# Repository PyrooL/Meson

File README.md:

# Meson
A split 3x14 keyboard with spacebars on a fourth row. Reversible MX//Alps/Choc support.

KiCAD libraries here:

- https://github.com/ai03-2725/MX_Alps_Hybrid.pretty

- https://github.com/ai03-2725/Type-C.pretty

- https://github.com/ai03-2725/random-keyboard-parts.pretty

- https://github.com/keebio/Keebio-Parts.pretty

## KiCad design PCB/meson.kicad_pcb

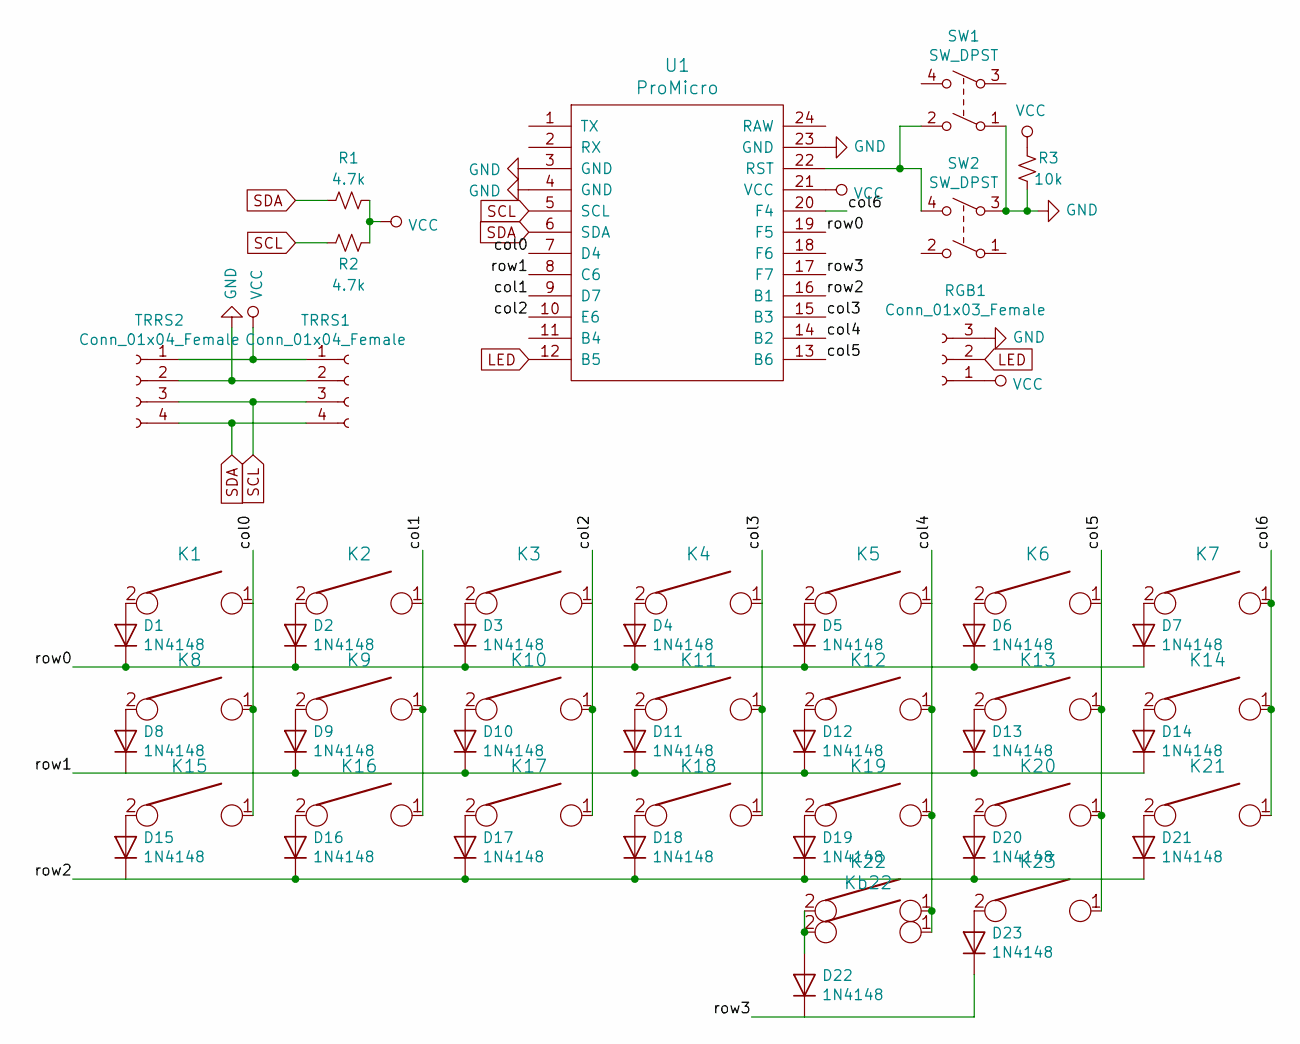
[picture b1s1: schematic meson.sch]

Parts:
D1, D2, D3, D4, D5, D6, D7, D8, D9, D10, D11, D12, D13, D14, D15, D16, D17, D18, D19, D20, D21, D22, D23: 1N4148; D_DO-35_SOD27_P7.62mm_Horizontal
K1, K2, K3, K4, K5, K6, K7, K8, K9, K10, K11, K12, K13, K14, K15, K16, K17, K18, K19, K20, K21, K22, K23: KEYSW; MX-Alps-Choc-1U-NoLED-Reversible
Kb22: KEYSW; MX-1U-NoLED-Reversible
R1, R2: 4.7k; Resistor-Hybrid
R3: 10k; Resistor-Hybrid
RGB1: Conn_01x03_Female; PinHeader_1x03_P2.54mm_Vertical
SW1, SW2: SW_DPST; SKQG-1155865
TRRS1, TRRS2: Conn_01x04_Female; TRRS-PJ-320A
U1: ProMicro; ArduinoProMicro

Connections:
/col0: K1.1, K8.1, K15.1, U1.7 (D4)
/col1: K2.1, K9.1, K16.1, U1.9 (D7)
/col2: K3.1, K10.1, K17.1, U1.10 (E6)
/col3: K4.1, K11.1, K18.1, U1.15 (B3)
/col4: K5.1, K12.1, K19.1, K22.1, Kb22.1, U1.14 (B2)
/col5: K6.1, K13.1, K20.1, K23.1, U1.13 (B6)
/col6: K7.1, K14.1, K21.1, U1.20 (F4)
/row0: D1.1 (K), D2.1 (K), D3.1 (K), D4.1 (K), D5.1 (K), D6.1 (K), D7.1 (K), U1.19 (F5)
/row1: D8.1 (K), D9.1 (K), D10.1 (K), D11.1 (K), D12.1 (K), D13.1 (K), D14.1 (K), U1.8 (C6)
/row2: D15.1 (K), D16.1 (K), D17.1 (K), D18.1 (K), D19.1 (K), D20.1 (K), D21.1 (K), U1.16 (B1)
/row3: D22.1 (K), D23.1 (K), U1.17 (F7)
GND: R3.2, RGB1.3, SW1.1, SW2.3, TRRS1.2, TRRS2.2, U1.3 (GND), U1.4 (GND), U1.23 (GND)
LED: RGB1.2, U1.12 (B5)
unnamed: D1.2 (A), K1.2
unnamed: D2.2 (A), K2.2
unnamed: D3.2 (A), K3.2
unnamed: D4.2 (A), K4.2
unnamed: D5.2 (A), K5.2
unnamed: D6.2 (A), K6.2
unnamed: D7.2 (A), K7.2
unnamed: D8.2 (A), K8.2
unnamed: D9.2 (A), K9.2
unnamed: D10.2 (A), K10.2
unnamed: D11.2 (A), K11.2
unnamed: D12.2 (A), K12.2
unnamed: D13.2 (A), K13.2
unnamed: D14.2 (A), K14.2
unnamed: D15.2 (A), K15.2
unnamed: D16.2 (A), K16.2
unnamed: D17.2 (A), K17.2
unnamed: D18.2 (A), K18.2
unnamed: D19.2 (A), K19.2
unnamed: D20.2 (A), K20.2
unnamed: D21.2 (A), K21.2
unnamed: D22.2 (A), K22.2, Kb22.2
unnamed: D23.2 (A), K23.2
unnamed: SW1.2, SW2.4, U1.22 (RST)
SCL: R2.2, TRRS1.3, TRRS2.3, U1.5 (SCL)
SDA: R1.2, TRRS1.4, TRRS2.4, U1.6 (SDA)
VCC: R1.1, R2.1, R3.1, RGB1.1, TRRS1.1, TRRS2.1, U1.21 (VCC)

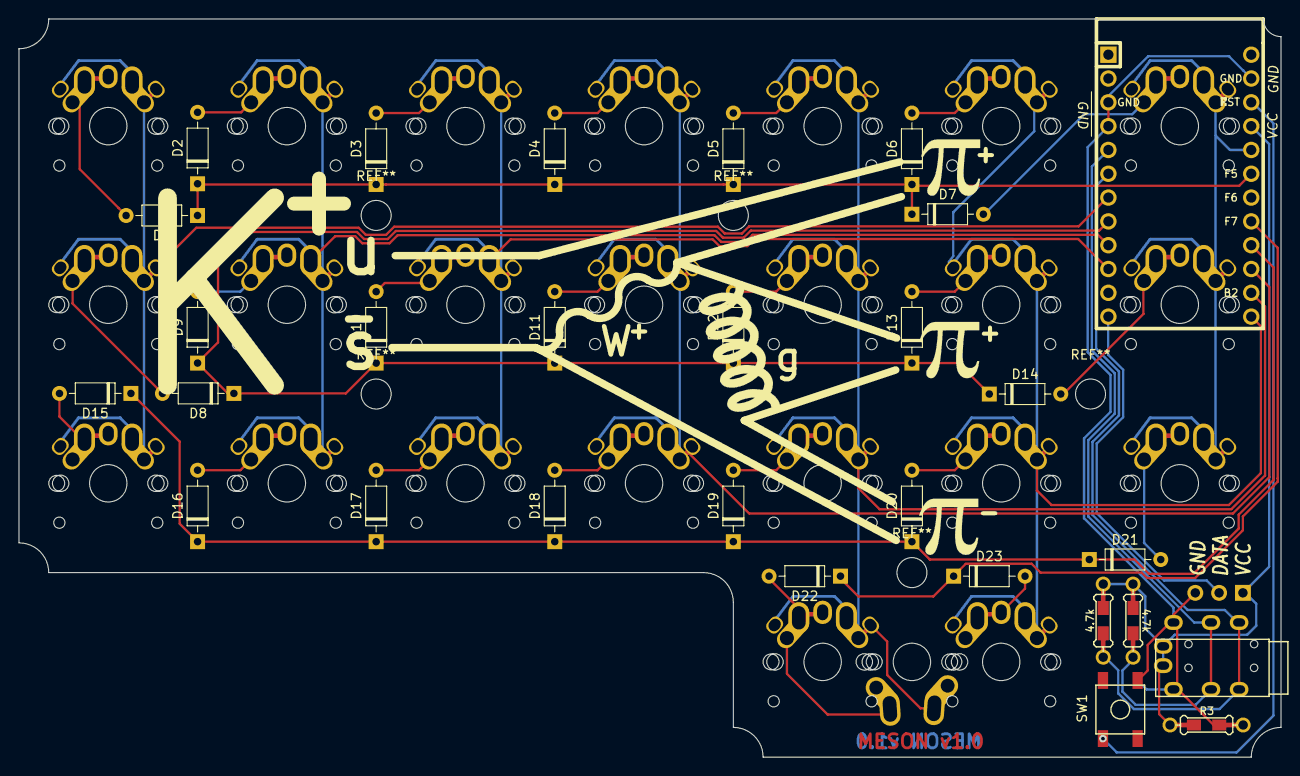
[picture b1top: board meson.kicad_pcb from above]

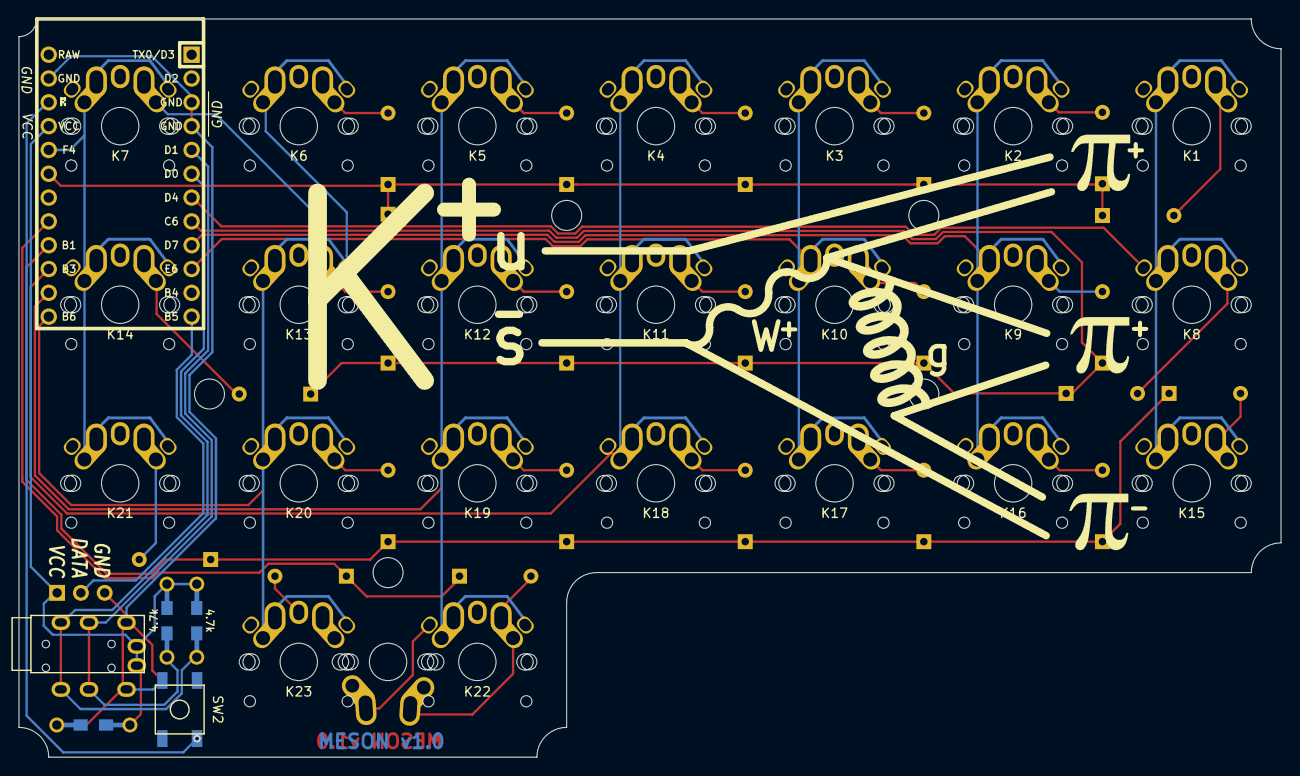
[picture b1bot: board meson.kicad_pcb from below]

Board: 2 copper layers, 134.6 x 78.7 mm, 56 parts (2 on the bottom side), 40 nets.

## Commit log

2019-04-17 Prototype PCB complete
2019-04-17 tidy up and bom
2019-04-17 Readme
2019-04-17 folders
2019-04-17 Create LICENSE
2019-04-17 gerbers yey
2019-04-18 "M3 mounting holes for pcb mounting+fixing big mistakes"
2019-04-18 cleaning
2019-04-19 "Gerbers for proto"
2019-07-19 moving towards production
